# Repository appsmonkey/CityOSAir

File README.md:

# CityOSAir

W**elcome to the CityOSAir github!**

Thank you for your interest in creating your own CityOSAir device. In order to join the clean air movement, we will walk you through this step-by-step guide on creating your own device.

Here you will learn how to create your own circuit board or order already made ones, how and where to get an enclosure for the device and, finally, how to setup your new device.

To help spread clean air everywhere, we are giving away all of our code as open source software and hardware. We invite all developers to collaborate and build upon our project. 
Everything you need to get started and become a part of our global movement is listed below.

## Getting started

* [Ordering your board](https://github.com/appsmonkey/CityOSAir/wiki/Board)

* [3D printing your enclosure] (https://github.com/appsmonkey/CityOSAir/wiki/Enclosure)

* [Setting up the device] (https://github.com/appsmonkey/CityOSAir/wiki/Setup)

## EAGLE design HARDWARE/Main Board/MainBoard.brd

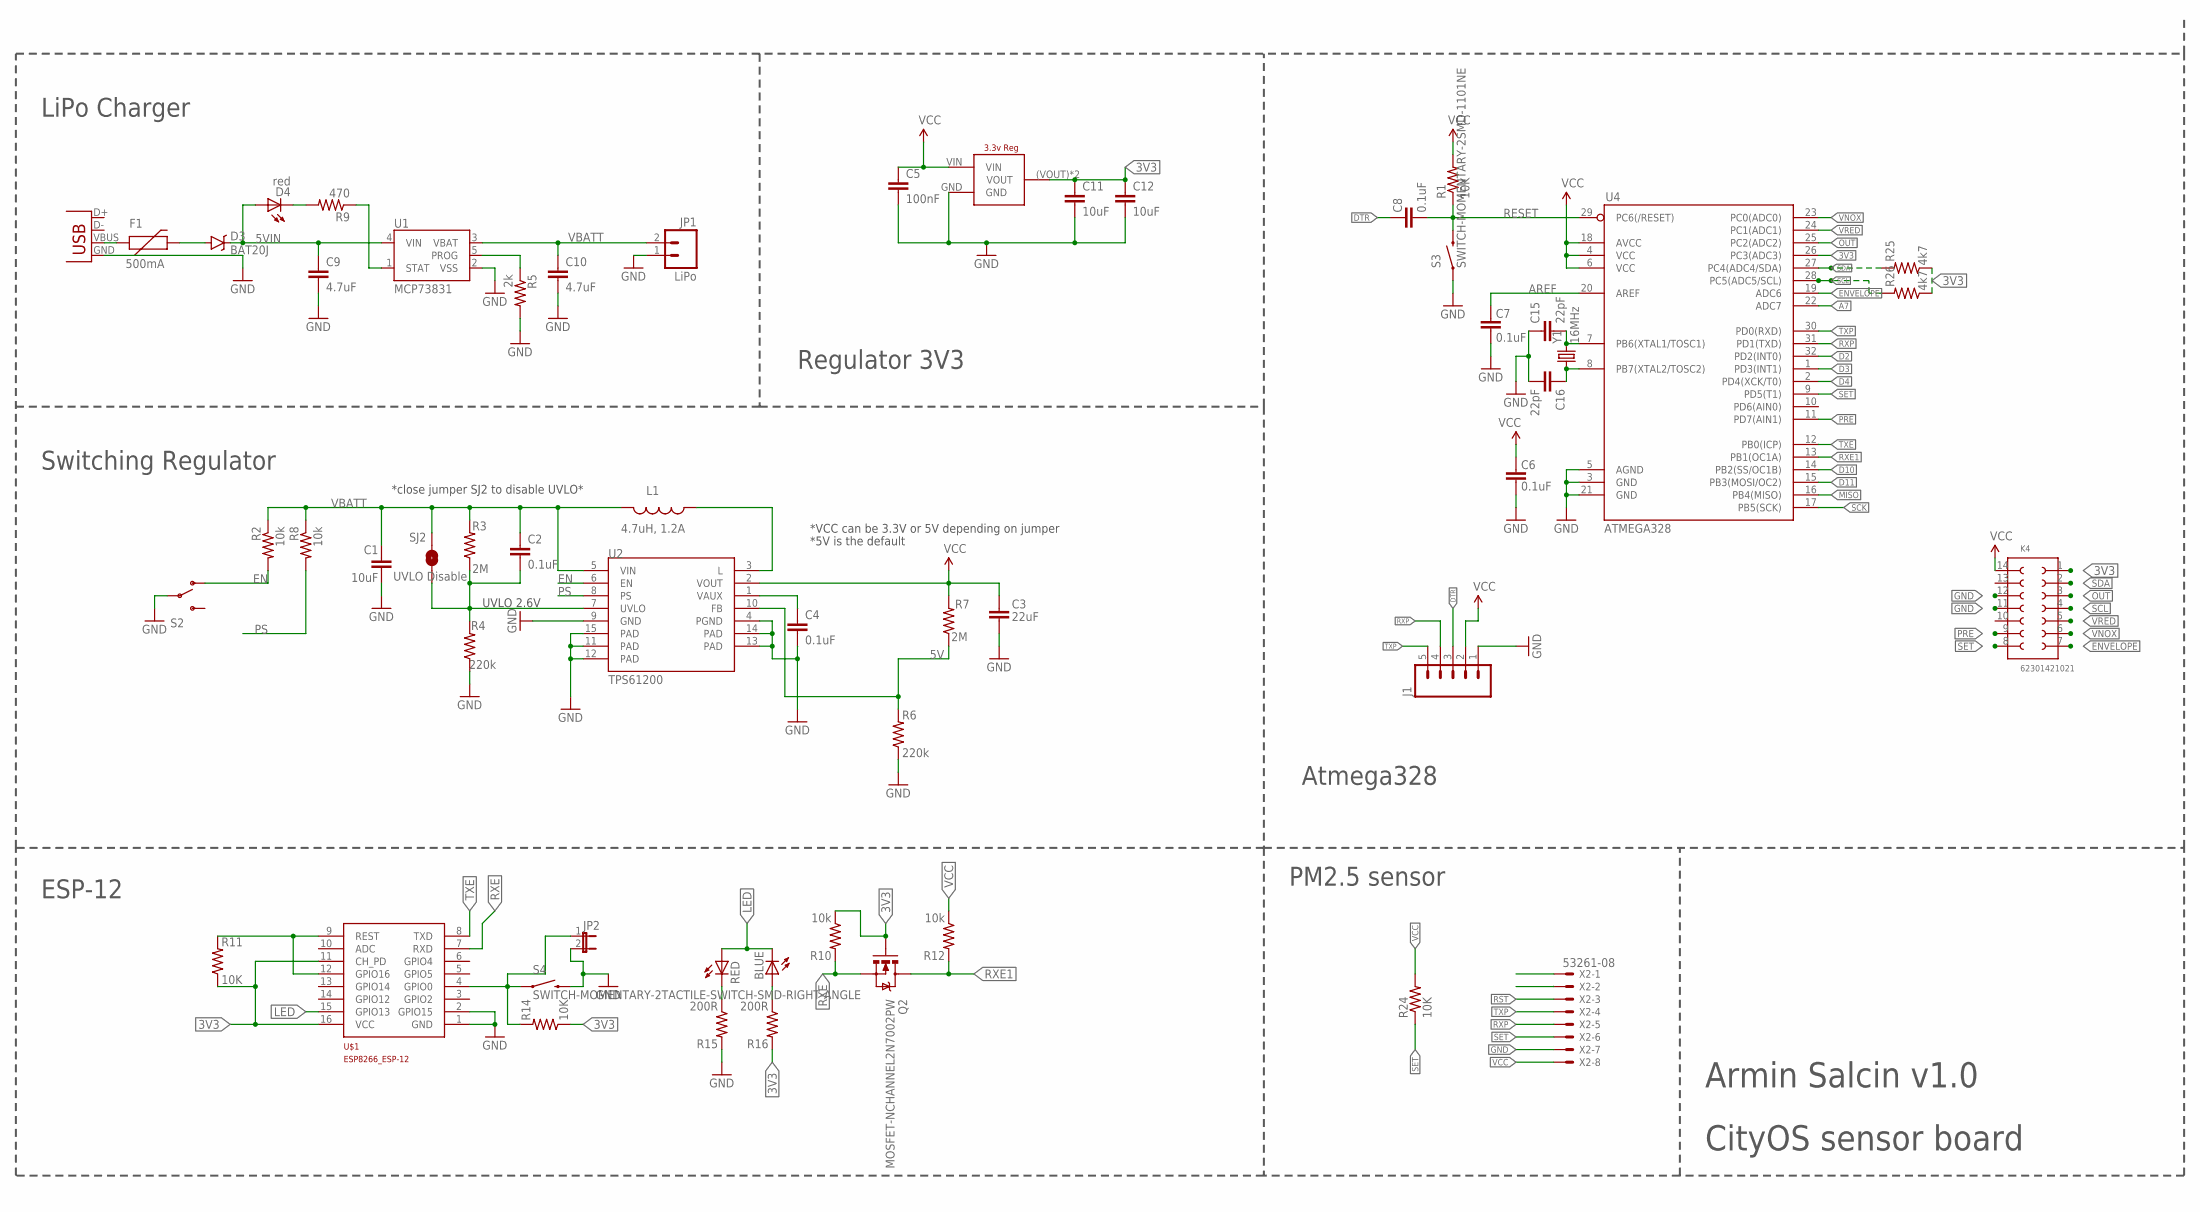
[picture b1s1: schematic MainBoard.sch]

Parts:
BLUE: LEDCHIPLED_0805; CHIPLED_0805
C1, C12: 10uF; 1206
C2, C4: 0.1uF; 0402-CAP
C3: 22uF; 0805
C5: 100nF; 0402-CAP
C6, C7, C8: 0.1uF; 0603-CAP
C9, C10: 4.7uF; 0402-CAP
C11: 10uF; 0402-CAP
C15, C16: 22pF; 0603-CAP
D3: BAT20J; SOD-323
D4: red; LED-0603
F1: 500mA; 0603
J1: M05PTH; 1X05
JP1: LiPo; JST-2-SMD
JP2: JUMPER-2PTH; 1X02
K4: 62301421021
L1: 4.7uH, 1.2A; CDRH2D09
Q2: MOSFET-NCHANNEL2N7002PW; SOT323
R1, R24: 10K; 0603-RES
R2, R8, R10, R12: 10k; 0402-RES
R3, R7: 2M; 0402-RES
R4, R6: 220k; 0402-RES
R5: 2k; 0402-RES
R9: 470; 0402-RES
R11, R14: 10K; 0402-RES
R15, R16: 200R; 0402-RES
R25, R26: 4k7; 0402-RES
RED: LEDCHIPLED_0805; CHIPLED_0805
S2: SWITCH-SPDT-SMD-A; SWITCH-SPST-SMD-A
S3: SWITCH-MOMENTARY-2SMD-1101NE; TACTILE-SWITCH-1101NE
S4: SWITCH-MOMENTARY-2TACTILE-SWITCH-SMD-RIGHT-ANGLE; TACTILE_SWITCH-SMD-RIGHT-ANGLE
SJ2: UVLO Disable; SJ_2S-NO
U1: MCP73831; SOT23-5
U2: TPS61200; QFN-10_PAD
U4: ATMEGA328; TQFP32-08
U$1: ESP8266_ESP-12; ESP8266-ESP12
U$2: LD1117; LD1117SOT-223
X1: USB-MICROB
X2: 53261-08
Y1: 16MHz; CRYSTAL-SMD-5X3

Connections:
3V3: C11.1, C12.1, K4.1, Q2.1 (G), R10.1, R11.1, R14.1, R16.2, R25.1, R26.1, U4.26 (PC3(ADC3)), U$1.11 (CH_PD), U$1.16 (VCC), U$2.(VOUT) (VOUT), U$2.VOUT
5V: R6.2, R7.1, U2.10 (FB)
5VIN: C9.1, D3.C, D4.A, U1.4 (VIN)
A7: U4.22 (ADC7)
AREF: C7.2, U4.20 (AREF)
D2: U4.32 (PD2(INT0))
D3: U4.1 (PD3(INT1))
D4: U4.2 (PD4(XCK/T0))
D10: U4.14 (PB2(SS/OC1B))
D11: U4.15 (PB3(MOSI/OC2))
DTR: C8.2, J1.3
EN: R2.2, S2.1 (O), U2.6 (EN)
ENVELOPE: K4.7, U4.19 (ADC6)
GND: C1.2, C3.2, C4.2, C5.2, C6.1, C7.1, C9.2, C10.2, C11.2, C12.2, C15.1, C16.2, J1.1, JP1.1, JP2.2, K4.11, K4.12, R4.1, R5.2, R6.1, R15.2, S2.2, S3.1, S4.2, U1.2 (VSS), U2.4 (PGND), U2.9 (GND), U2.11 (PAD), U2.12 (PAD), U2.13 (PAD), U2.14 (PAD), U2.15 (PAD), U4.3 (GND), U4.5 (AGND), U4.21 (GND), U$1.1 (GND), U$1.2 (GPIO15), U$2.GND, X1.GND, X2.7
LED: BLUE.C, RED.A, U$1.15 (GPIO13)
MISO: U4.16 (PB4(MISO))
unnamed: C4.1, U2.1 (VAUX)
unnamed: L1.P$1 (1), U2.3 (L)
unnamed: C16.1, U4.8 (PB7(XTAL2/TOSC2)), Y1.1
unnamed: C15.2, U4.7 (PB6(XTAL1/TOSC1)), Y1.3 (2)
unnamed: JP2.1, R14.2, S4.1, U$1.4 (GPIO0)
unnamed: R11.2, U$1.9 (REST), U$1.12 (GPIO16)
unnamed: F1.1, X1.VBUS
unnamed: D4.C, R9.2
unnamed: R15.1, RED.C
unnamed: BLUE.A, R16.1
unnamed: R5.1, U1.5 (PROG)
unnamed: D3.A, F1.2
unnamed: R9.1, U1.1 (STAT)
OUT: K4.3, U4.25 (PC2(ADC2))
PRE: K4.9, U4.11 (PD7(AIN1))
PS: R8.2, U2.8 (PS)
RESET: C8.1, R1.1, S3.2, U4.29 (PC6(/RESET))
RST: X2.3
RXE: Q2.2 (S), R10.2, U$1.7 (RXD)
RXE1: Q2.3 (D), R12.2, U4.13 (PB1(OC1A))
RXP: J1.4, U4.31 (PD1(TXD)), X2.5
SCK: U4.17 (PB5(SCK))
SCL: K4.4, R26.2, U4.28 (PC5(ADC5/SCL))
SDA: K4.2, R25.2, U4.27 (PC4(ADC4/SDA))
SET: K4.8, R24.1, U4.9 (PD5(T1)), X2.6
TXE: U4.12 (PB0(ICP)), U$1.8 (TXD)
TXP: J1.5, U4.30 (PD0(RXD)), X2.4
UVLO: C2.2, R3.1, R4.2, SJ2.1, U2.7 (UVLO)
VBATT: C1.1, C2.1, C10.1, JP1.2, L1.P$2 (2), R2.1, R3.2, R8.1, SJ2.2, U1.3 (VBAT), U2.5 (VIN)
VCC: C3.1, C5.1, C6.2, J1.2, K4.14, R1.2, R7.2, R12.1, R24.2, U2.2 (VOUT), U4.4 (VCC), U4.6 (VCC), U4.18 (AVCC), U$2.VIN, X2.8
VNOX: K4.6, U4.23 (PC0(ADC0))
VRED: K4.5, U4.24 (PC1(ADC1))

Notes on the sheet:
UVLO 2.6V
*close jumper SJ2 to disable UVLO*
LiPo Charger
Switching Regulator
*VCC can be 3.3V or 5V depending on jumper
*5V is the default
Regulator 3V3
ESP-12
Atmega328
PM2.5 sensor
Armin Salcin v1.0
CityOS sensor board

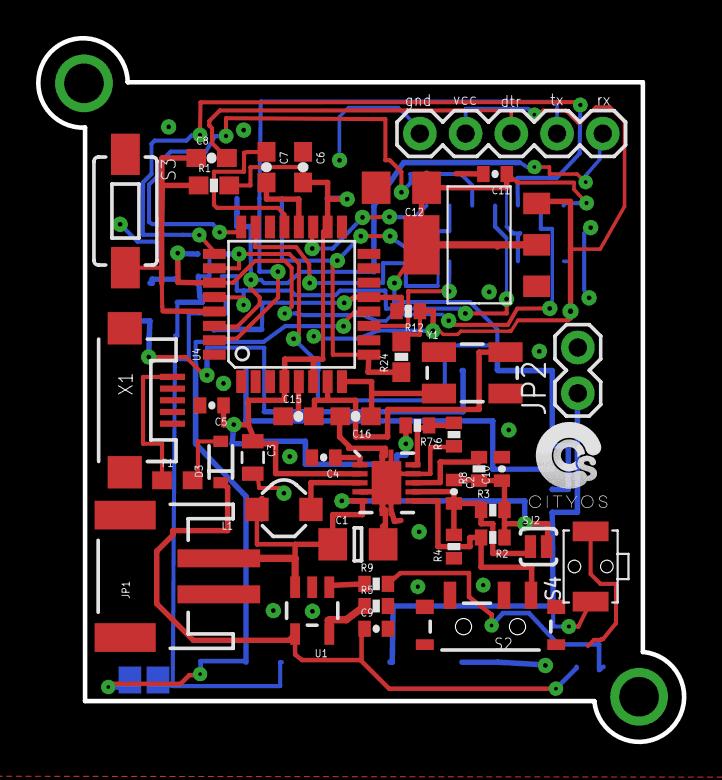
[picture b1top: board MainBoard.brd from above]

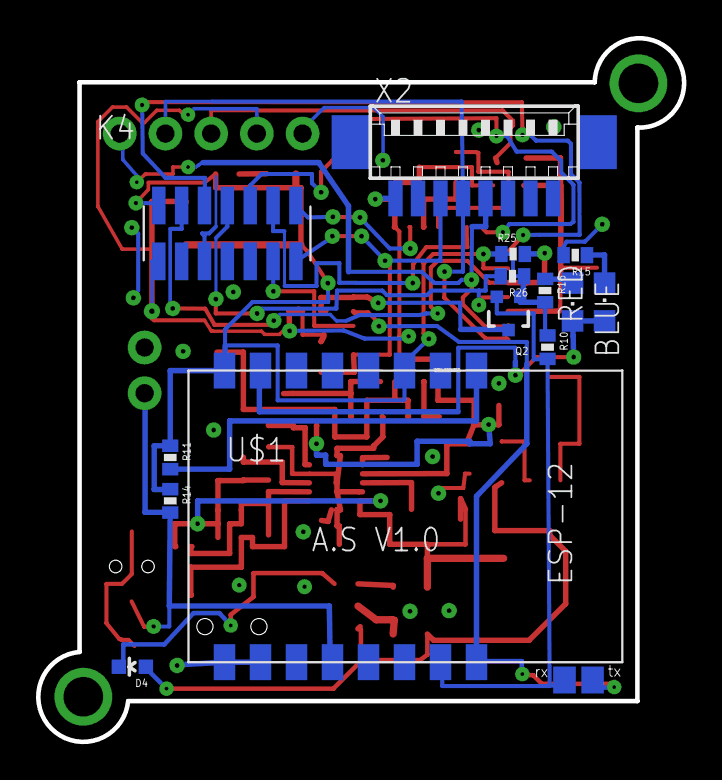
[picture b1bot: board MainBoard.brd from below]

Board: 2 copper layers, 35.9 x 39.1 mm, 55 parts (14 on the bottom side), 39 nets.

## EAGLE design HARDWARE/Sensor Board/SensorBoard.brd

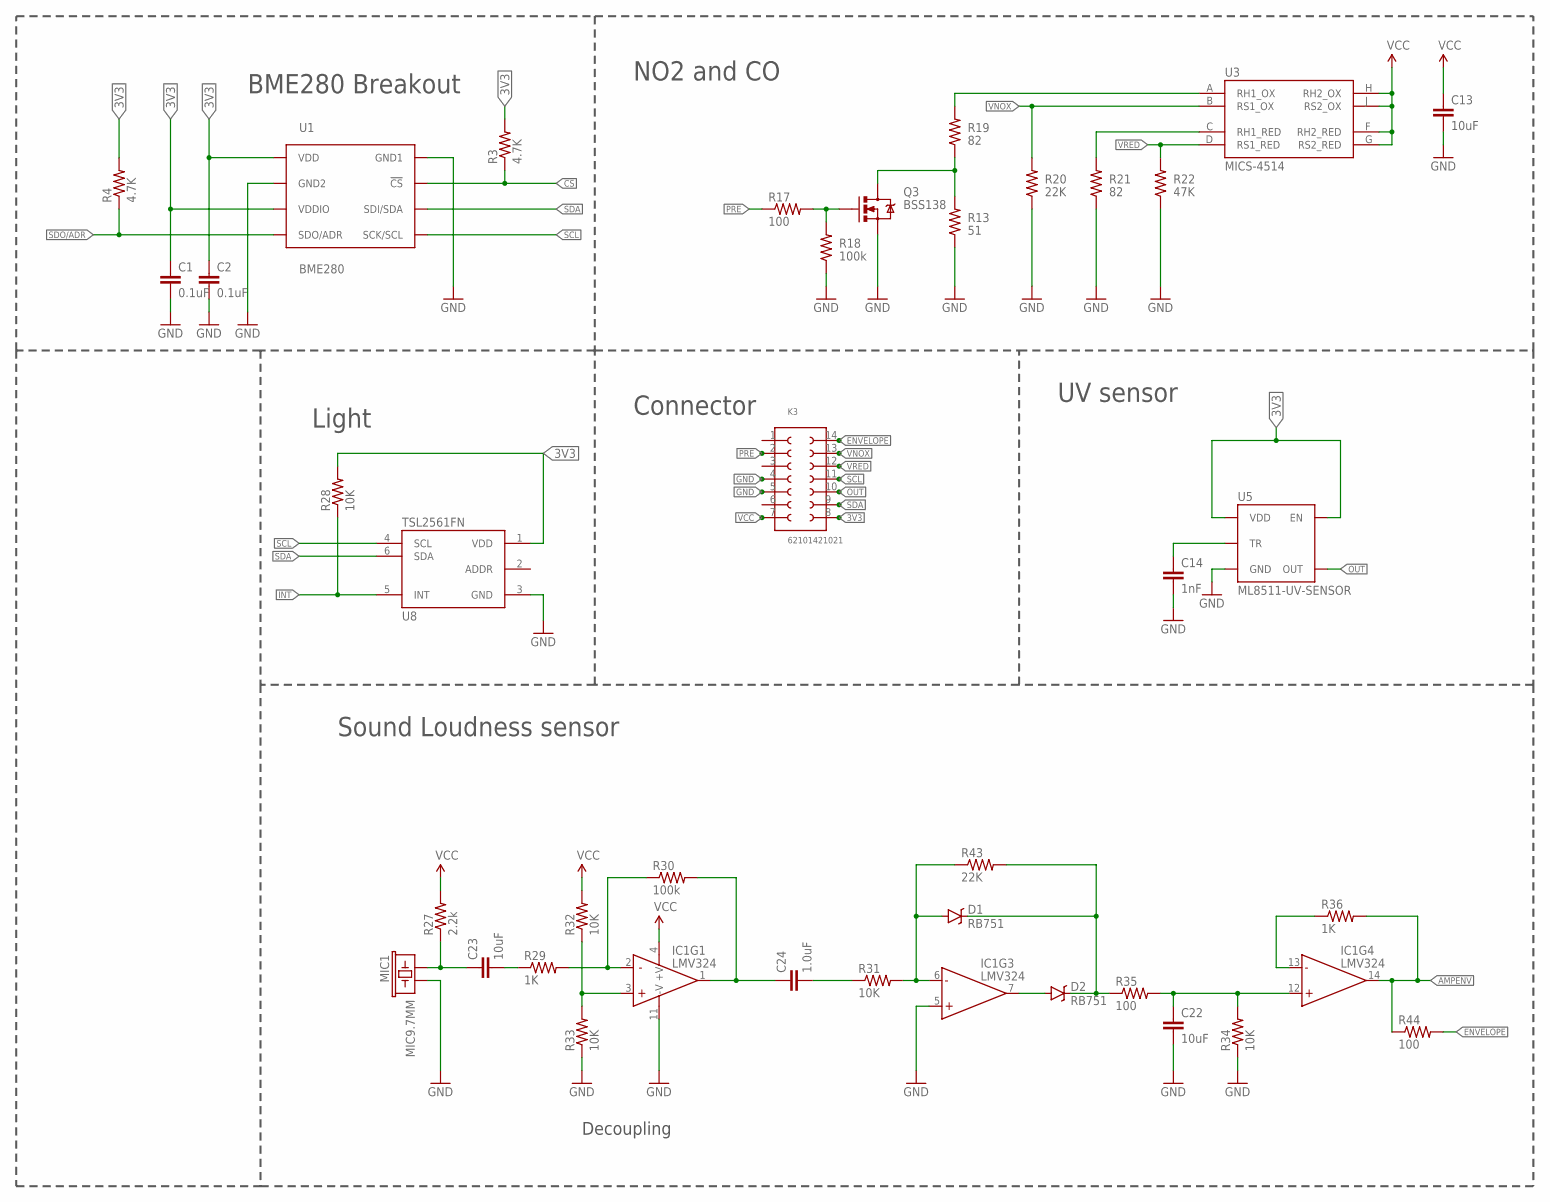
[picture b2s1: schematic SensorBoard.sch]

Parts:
C1, C2: 0.1uF; 0603-CAP
C13: 10uF; 0805
C14: 1nF; 0603-CAP
C22, C23: 10uF; 1206
C24: 1.0uF; 0603-CAP
D1, D2: RB751; SOD-523
IC1: LMV324; SO014
K3: 62101421021
MIC1: MIC9.7MM; MIC-9.7MM
Q3: MOSFET-NCHANNELBSS138; SOT23-3
R3, R4: 4.7K; 0603-RES
R13: 51; 0603-RES
R17, R35, R44: 100; 0603-RES
R18, R30: 100k; 0603-RES
R19, R21: 82; 0805
R20, R43: 22K; 0603-RES
R22: 47K; 0603-RES
R27: 2.2k; 0603-RES
R28, R31, R32, R33, R34: 10K; 0603-RES
R29, R36: 1K; 0603-RES
U1: BME280; BME280_LGA
U3: MICS-4514; MICS_10-SMD
U5: ML8511-UV-SENSOR; ML8511
U8: TSL2561FN; FN-6

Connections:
3V3: C1.1, C2.1, C13.1, K3.8, R3.2, R4.2, R28.2, U1.P$6 (VDDIO), U1.P$8 (VDD), U3.F (RH2_RED), U3.G (RS2_RED), U3.H (RH2_OX), U3.J (RS2_OX), U5.4 (EN), U5.7 (VDD), U8.1 (VDD)
!CS: R3.1, U1.P$2 (!CS)
AMPENV: IC1.14 (OUT), R36.2, R44.1
ENVELOPE: K3.14, R44.2
GND: C1.2, C2.2, C13.2, C14.2, C22.2, IC1.5 (+IN), IC1.11 (-V), K3.4, K3.5, MIC1.2, Q3.2 (S), R13.1, R18.1, R20.1, R21.1, R22.1, R33.1, R34.1, U1.P$1 (GND1), U1.P$7 (GND2), U5.5 (GND), U8.3 (GND)
INT: R28.1, U8.5 (INT)
N$: C24.1, IC1.1 (OUT), R30.2
unnamed: Q3.3 (D), R13.2, R19.1
unnamed: Q3.1 (G), R17.2, R18.2
unnamed: R19.2, U3.A (RH1_OX)
unnamed: R21.2, U3.C (RH1_RED)
unnamed: C14.1, U5.10 (TR)
unnamed: C23.1, MIC1.1, R27.1
unnamed: IC1.3 (+IN), R32.1, R33.2
unnamed: IC1.2 (-IN), R29.2, R30.1
unnamed: C23.2, R29.1
unnamed: C24.2, R31.1
unnamed: D1.A, IC1.6 (-IN), R31.2, R43.1
unnamed: D2.A, IC1.7 (OUT)
unnamed: D1.C, D2.C, R35.1, R43.2
unnamed: C22.1, IC1.12 (+IN), R34.2, R35.2
unnamed: IC1.13 (-IN), R36.1
OUT: K3.10, U5.8 (OUT)
PRE: K3.2, R17.1
SCL: K3.11, U1.P$4 (SCK/SCL), U8.4 (SCL)
SDA: K3.9, U1.P$3 (SDI/SDA), U8.6 (SDA)
SDO/ADR: R4.1, U1.P$5 (SDO/ADR)
VCC: IC1.4 (+V), K3.7, R27.2, R32.2
VNOX: K3.13, R20.2, U3.B (RS1_OX)
VRED: K3.12, R22.2, U3.D (RS1_RED)

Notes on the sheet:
NO2 and CO
UV sensor
Light
Decoupling
BME280 Breakout
Sound Loudness sensor
Connector

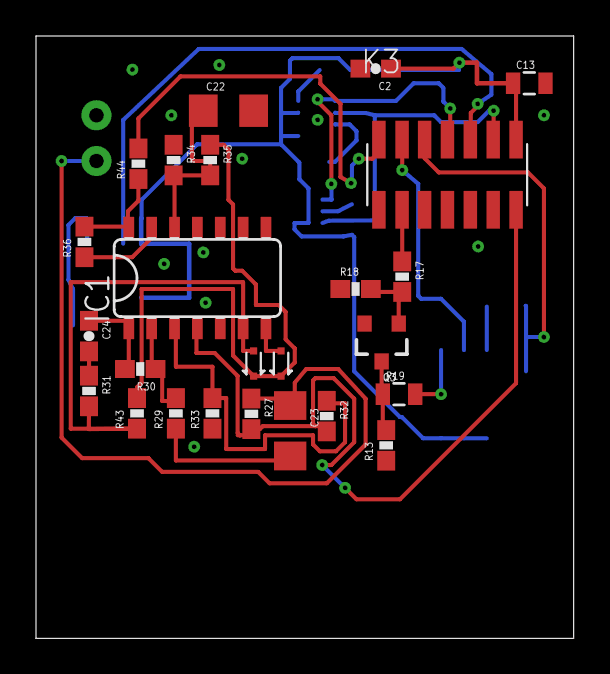
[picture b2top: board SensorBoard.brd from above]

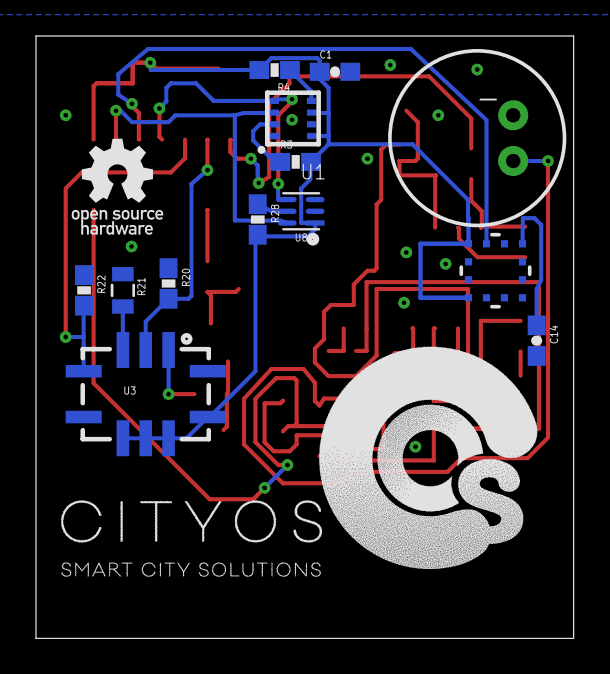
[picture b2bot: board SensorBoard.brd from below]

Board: 2 copper layers, 29.9 x 33.5 mm, 38 parts (13 on the bottom side), 30 nets.

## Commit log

2016-08-30 Added new PCB files
2016-08-30 New commit message
2016-08-31 Create 3D
2016-08-31 new folder for 3d design
2016-08-31 Device photos
2016-08-31 add BOM files
2016-08-31 put picture in existing folder
2016-08-31 edited readme file
2016-08-31 add new name to folder
2016-08-31 Create sss
2016-08-31 added new folder
2016-08-31 edit readme
2016-09-03 Create 1
2016-09-03 background wiki
2016-09-03 Create Datasheets
2016-09-03 Rename HARDWARE/Wiki/Datasheets/1 to HARDWARE/Wiki/Datasheet/111
2016-09-03 add gerber files
2016-09-06 Create app
2016-09-08 model screenshots
2016-10-31 - added DS_Store to gitignore
2016-10-31 - added CityOS Air iOS app
2016-11-02 - changed chart loading text colour to white - localised date formatter for graph x axis timestamp - set keyboard type for email input field - increased build number for project
2016-11-04 - refactored function to set data for chart
2016-11-04 - user model updated with new properties
2016-11-04 - user manager updated to save new user object
2016-11-04 - add loging in of user at startup to refresh token
2016-11-07 - created ReadingCollection model
2016-11-07 - updated Readings model to conform to Realm requirements
2016-11-07 - created Cache util to save and retrieve data
2016-11-07 - project tree changes
2016-11-07 - updated AirService to use Cache util
2016-11-07 - updated DeviceViewController to use data from cache
2016-11-07 - removed unnecessary stuff
2016-11-07 - UI tweaks for table view cell and graph message when no data to show
2016-11-07 - updated build number and submitted new test flight build
2016-12-20 - added Balloon marker for chart
2016-12-20 - implemented marker and some display logic in ChartView
2016-12-20 - added hide keyboard functionality to extensions - added close on loading screen
2016-12-20 - implemented hide keyboard
2016-12-20 - implemented terminate loading and observers to stop loading when app goes into background
2016-12-20 - UI tweaks
2016-12-20 - added crashlytics - updated pods
2016-12-20 - implemented crashlytics
2016-12-20 - implemented status code handling in responses - implemented status code in completion blocks
2016-12-20 - implemented new error messages for login
2016-12-20 - added debug information format to be "dwarf-with-dsym" for Fabric
2017-01-05 - removed unused assets
2017-01-05 - added new styles and texts
2017-01-05 - added new extensions and enums
2017-01-05 - removing some old and adding new assets
2017-01-05 - added gauge view - added gauge states
2017-01-05 - added side menu
2017-01-05 - updated login screen and some logic
2017-01-05 - added api controller, cell and model
2017-01-05 - changes and additions
2017-01-06 - added device model and updated network service
2017-01-06 - updated depending on changes from before
2017-01-06 - taken care of app flow - reworked gauge logic and AQI with states
2017-01-06 - new user logic - updated styles and texts - updated models - added helper functions - cell logic - UI tweaks
2017-01-08 - firebase setup - notifications setup - settings cells created - settings action for notifications
2017-01-14 - added loading - added gif helper - added Switch table view cell - added AlertsViewController
2017-01-14 - subscribing every user to 'broadcast' topic
2017-01-14 - fixing bugs and typos - implemented loading - added some loading logic
2017-01-17 - project structure change
2017-01-31 - final before moving to new repository

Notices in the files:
parts and their libraries:
SparkFun-Passives: Licensing: CC v3.0 Share-Alike You are welcome to use this library for commercial purposes.
SparkFun-Electromechanical: Licensing: Creative Commons ShareAlike 4.0 International - https://creativecommons.org/licenses/by-sa/4.0
